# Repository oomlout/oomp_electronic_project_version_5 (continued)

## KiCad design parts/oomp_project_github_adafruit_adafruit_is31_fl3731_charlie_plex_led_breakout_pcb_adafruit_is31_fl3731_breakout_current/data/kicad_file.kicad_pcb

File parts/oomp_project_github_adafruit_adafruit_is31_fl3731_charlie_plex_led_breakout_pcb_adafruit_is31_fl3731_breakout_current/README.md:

# Project adafruit/Adafruit-IS31FL3731-CharliePlex-LED-Breakout-PCB Adafruit IS31 FL3731 Breakout current

[View the project on GitHub](https://github.com/adafruit/Adafruit-IS31FL3731-CharliePlex-LED-Breakout-PCB/blob/master/Adafruit%20IS31FL3731%20Breakout.brd)

[Open the interactive board explorer (GitHub Pages)](https://oomlout.github.io/oomp_electronic_project_version_5/parts/oomp_project_github_adafruit_adafruit_is31_fl3731_charlie_plex_led_breakout_pcb_adafruit_is31_fl3731_breakout_current/board_explorer.html)

[Browse this project category](../../navigation/oomp/project/github/adafruit/adafruit_is31_fl3731_charlie_plex_led_breakout_pcb/adafruit_is31_fl3731_breakout/README.md)

Project adafruit/Adafruit-IS31FL3731-CharliePlex-LED-Breakout-PCB Adafruit IS31 FL3731 Breakout current is a KiCad project containing 39 extracted component records. The catalogue matcher linked 18 physical placements to OOMP parts.

## Project snapshot

| Item | Count |
| --- | ---: |
| Components | 39 |
| PCB footprints | 26 |
| Mounting and locating holes | 4 |
| Matched OOMP mounting-hole items | 4 |
| Schematic symbols | 38 |
| Matched OOMP components | 18 |
| Unmatched physical components | 1 |
| Front-side placements | 15 |
| Back-side placements | 0 |
| Project version | `current` |
| Git ref | `master` |

## Board

[Original KiCad files](https://github.com/oomlout/oomp_electronic_project_version_5/tree/main/parts/oomp_project_github_adafruit_adafruit_is31_fl3731_charlie_plex_led_breakout_pcb_adafruit_is31_fl3731_breakout_current/data/original) · [OOMP KiCad design and local libraries](https://github.com/oomlout/oomp_electronic_project_version_5/tree/main/parts/oomp_project_github_adafruit_adafruit_is31_fl3731_charlie_plex_led_breakout_pcb_adafruit_is31_fl3731_breakout_current/data/oomp_design) · [Conversion / skipped-item report](https://github.com/oomlout/oomp_electronic_project_version_5/blob/main/parts/oomp_project_github_adafruit_adafruit_is31_fl3731_charlie_plex_led_breakout_pcb_adafruit_is31_fl3731_breakout_current/data/oomp_design/conversion_report.yaml)

The OOMP design is a separate copy. Only symbols and footprints verified against unchanged installed KiCad masters are replaced; custom and modified items are retained.

- Approximate size: **43.18 mm × 27.94 mm**
- Outline source: `KiCad Edge.Cuts`
- Placement drawing: [view `board.svg`](https://github.com/oomlout/oomp_electronic_project_version_5/blob/main/parts/oomp_project_github_adafruit_adafruit_is31_fl3731_charlie_plex_led_breakout_pcb_adafruit_is31_fl3731_breakout_current/data/generated_data/src/board.svg)
- PNG placement drawing: [view `board.png`](https://github.com/oomlout/oomp_electronic_project_version_5/blob/main/parts/oomp_project_github_adafruit_adafruit_is31_fl3731_charlie_plex_led_breakout_pcb_adafruit_is31_fl3731_breakout_current/data/generated_data/src/board.png)
- 300-pixel placement preview: [view `board_300.png`](https://github.com/oomlout/oomp_electronic_project_version_5/blob/main/parts/oomp_project_github_adafruit_adafruit_is31_fl3731_charlie_plex_led_breakout_pcb_adafruit_is31_fl3731_breakout_current/data/generated_data/src/board_300.png)
- Placement drawing with pin names: [view `board_pins.svg`](https://github.com/oomlout/oomp_electronic_project_version_5/blob/main/parts/oomp_project_github_adafruit_adafruit_is31_fl3731_charlie_plex_led_breakout_pcb_adafruit_is31_fl3731_breakout_current/data/generated_data/src/board_pins.svg)
- PNG drawing with pin names: [view `board_pins.png`](https://github.com/oomlout/oomp_electronic_project_version_5/blob/main/parts/oomp_project_github_adafruit_adafruit_is31_fl3731_charlie_plex_led_breakout_pcb_adafruit_is31_fl3731_breakout_current/data/generated_data/src/board_pins.png)
- 300-pixel pin preview: [view `board_pins_300.png`](https://github.com/oomlout/oomp_electronic_project_version_5/blob/main/parts/oomp_project_github_adafruit_adafruit_is31_fl3731_charlie_plex_led_breakout_pcb_adafruit_is31_fl3731_breakout_current/data/generated_data/src/board_pins_300.png)
- Bottom placement drawing: [view `board_bottom.svg`](https://github.com/oomlout/oomp_electronic_project_version_5/blob/main/parts/oomp_project_github_adafruit_adafruit_is31_fl3731_charlie_plex_led_breakout_pcb_adafruit_is31_fl3731_breakout_current/data/generated_data/src/board_bottom.svg)
- Bottom PNG placement drawing: [view `board_bottom.png`](https://github.com/oomlout/oomp_electronic_project_version_5/blob/main/parts/oomp_project_github_adafruit_adafruit_is31_fl3731_charlie_plex_led_breakout_pcb_adafruit_is31_fl3731_breakout_current/data/generated_data/src/board_bottom.png)
- 300-pixel bottom preview: [view `board_bottom_300.png`](https://github.com/oomlout/oomp_electronic_project_version_5/blob/main/parts/oomp_project_github_adafruit_adafruit_is31_fl3731_charlie_plex_led_breakout_pcb_adafruit_is31_fl3731_breakout_current/data/generated_data/src/board_bottom_300.png)
- Bottom placement drawing with pin names: [view `board_pins_bottom.svg`](https://github.com/oomlout/oomp_electronic_project_version_5/blob/main/parts/oomp_project_github_adafruit_adafruit_is31_fl3731_charlie_plex_led_breakout_pcb_adafruit_is31_fl3731_breakout_current/data/generated_data/src/board_pins_bottom.svg)
- Bottom PNG drawing with pin names: [view `board_pins_bottom.png`](https://github.com/oomlout/oomp_electronic_project_version_5/blob/main/parts/oomp_project_github_adafruit_adafruit_is31_fl3731_charlie_plex_led_breakout_pcb_adafruit_is31_fl3731_breakout_current/data/generated_data/src/board_pins_bottom.png)
- 300-pixel bottom pin preview: [view `board_pins_bottom_300.png`](https://github.com/oomlout/oomp_electronic_project_version_5/blob/main/parts/oomp_project_github_adafruit_adafruit_is31_fl3731_charlie_plex_led_breakout_pcb_adafruit_is31_fl3731_breakout_current/data/generated_data/src/board_pins_bottom_300.png)
- Mechanical drawing: [view `board_mechanical.svg`](https://github.com/oomlout/oomp_electronic_project_version_5/blob/main/parts/oomp_project_github_adafruit_adafruit_is31_fl3731_charlie_plex_led_breakout_pcb_adafruit_is31_fl3731_breakout_current/data/generated_data/src/board_mechanical.svg)
- Mechanical PNG: [view `board_mechanical.png`](https://github.com/oomlout/oomp_electronic_project_version_5/blob/main/parts/oomp_project_github_adafruit_adafruit_is31_fl3731_charlie_plex_led_breakout_pcb_adafruit_is31_fl3731_breakout_current/data/generated_data/src/board_mechanical.png)
- 300-pixel mechanical preview: [view `board_mechanical_300.png`](https://github.com/oomlout/oomp_electronic_project_version_5/blob/main/parts/oomp_project_github_adafruit_adafruit_is31_fl3731_charlie_plex_led_breakout_pcb_adafruit_is31_fl3731_breakout_current/data/generated_data/src/board_mechanical_300.png)
- Open the board explorer on GitHub Pages: [explore this board](https://oomlout.github.io/oomp_electronic_project_version_5/parts/oomp_project_github_adafruit_adafruit_is31_fl3731_charlie_plex_led_breakout_pcb_adafruit_is31_fl3731_breakout_current/board_explorer.html)
- InteractiveHtmlBom generation is configured; install KiCad or set `KICAD_PYTHON` to its bundled Python to build `data/interactivehtmlbom/ibom.html`.

## Board with pins

## Bottom board with pins

The bottom view is mirrored horizontally so it is shown as viewed from beneath the assembled board.

## Mechanical layer

The table uses a board-relative origin at the minimum X/Y point of `Edge.Cuts`. This point is shown as **0,0** in the mechanical drawing; X increases right and Y increases down. Original KiCad coordinates are retained alongside it.

### Diameter 2.5 mm holes

| OOMP reference | Source | Name | Classification | Role | Board X (mm) | Board Y (mm) | OOMP part |
| --- | --- | --- | --- | --- | ---: | ---: | --- |
| `MH1` | `U$3` | Mounting Hole 2.5 mm Round Plated | `mechanical / mounting_hole / 2_5_mm / round / plated` | mounting | 2.540 | 25.400 | [`mechanical_mounting_hole_2_5_mm_round_plated`](https://github.com/oomlout/oomp_electronic_version_5/tree/main/parts/mechanical_mounting_hole_2_5_mm_round_plated) |
| `MH2` | `U$4` | Mounting Hole 2.5 mm Round Plated | `mechanical / mounting_hole / 2_5_mm / round / plated` | mounting | 40.640 | 25.400 | [`mechanical_mounting_hole_2_5_mm_round_plated`](https://github.com/oomlout/oomp_electronic_version_5/tree/main/parts/mechanical_mounting_hole_2_5_mm_round_plated) |
| `MH3` | `U$5` | Mounting Hole 2.5 mm Round Plated | `mechanical / mounting_hole / 2_5_mm / round / plated` | mounting | 2.540 | 2.540 | [`mechanical_mounting_hole_2_5_mm_round_plated`](https://github.com/oomlout/oomp_electronic_version_5/tree/main/parts/mechanical_mounting_hole_2_5_mm_round_plated) |
| `MH4` | `U$6` | Mounting Hole 2.5 mm Round Plated | `mechanical / mounting_hole / 2_5_mm / round / plated` | mounting | 40.640 | 2.540 | [`mechanical_mounting_hole_2_5_mm_round_plated`](https://github.com/oomlout/oomp_electronic_version_5/tree/main/parts/mechanical_mounting_hole_2_5_mm_round_plated) |

## Bill of materials

| References | Quantity | Description | Value | Footprint | OOMP part |
| --- | ---: | --- | --- | --- | --- |
| C1, C4 | 2 | Capacitor 10 uF 0805 | 10uF | `Adafruit IS31FL3731 Breakout-import-fps:0805-NO` | [`electronic_capacitor_0805_10_micro_farad`](https://github.com/oomlout/oomp_electronic_version_5/tree/main/parts/electronic_capacitor_0805_10_micro_farad) |
| C2, C5 | 2 | Capacitor 100 nF 0805 | 0.1uF | `Adafruit IS31FL3731 Breakout-import-fps:0805-NO` | [`electronic_capacitor_0805_100_nano_farad`](https://github.com/oomlout/oomp_electronic_version_5/tree/main/parts/electronic_capacitor_0805_100_nano_farad) |
| C3 | 1 | Capacitor 220 nF 0805 | 0.22uF | `Adafruit IS31FL3731 Breakout-import-fps:0805-NO` | [`electronic_capacitor_0805_220_nano_farad`](https://github.com/oomlout/oomp_electronic_version_5/tree/main/parts/electronic_capacitor_0805_220_nano_farad) |
| JP2, JP4 | 2 | Connector Header PZ254-1-13-Z-8.5 |  | `Adafruit IS31FL3731 Breakout-import-fps:1X13_ROUND_70` | [`electronic_connector_header_2_54_mm_pitch_through_hole_13_pin`](https://github.com/oomlout/oomp_electronic_version_5/tree/main/parts/electronic_connector_header_2_54_mm_pitch_through_hole_13_pin) |
| JP5 | 1 | Connector Header PH2.54-01-07PZD |  | `Adafruit IS31FL3731 Breakout-import-fps:1X07_ROUND_76` | [`electronic_connector_header_2_54_mm_pitch_through_hole_7_pin`](https://github.com/oomlout/oomp_electronic_version_5/tree/main/parts/electronic_connector_header_2_54_mm_pitch_through_hole_7_pin) |
| R1 | 1 | Resistor 20000 Ohm 0805 | 20K | `Adafruit IS31FL3731 Breakout-import-fps:0805-THM` | [`electronic_resistor_0805_20000_ohm`](https://github.com/oomlout/oomp_electronic_version_5/tree/main/parts/electronic_resistor_0805_20000_ohm) |
| R2, R3, R4, R5, R6 | 5 | Resistor 20000 Ohm 0805 | 20K | `Adafruit IS31FL3731 Breakout-import-fps:0805-NO` | [`electronic_resistor_0805_20000_ohm`](https://github.com/oomlout/oomp_electronic_version_5/tree/main/parts/electronic_resistor_0805_20000_ohm) |
| U1 | 1 | IS31FL3731-SALS2 | IS31FL3731-SALS2 | `Adafruit IS31FL3731 Breakout-import-fps:QFN28_4MM_0.4MM` | unmatched |

## Main nets

| Net | Pads | Components |
| --- | ---: | --- |
| `VCC` | 11 | C1, C4, C5, JP2, JP5, R2, R3, R4, R5, SJ1, U1 |
| `GND` | 10 | C1, C2, C4, C5, JP2, JP5, R1, R6, U1 |
| `ADDR` | 6 | JP4, R6, SJ1, SJ2, SJ3, U1 |
| `SCL` | 5 | JP2, JP5, R4, SJ2, U1 |
| `SDA` | 5 | JP2, JP5, R3, SJ3, U1 |
| `INTB` | 4 | JP4, JP5, R5, U1 |
| `SHUTDOWN` | 4 | JP4, JP5, R2, U1 |
| `AUDIOIN` | 3 | C3, JP4, JP5 |
| `CA1` | 2 | JP4, U1 |
| `CA2` | 2 | JP4, U1 |
| `CA3` | 2 | JP4, U1 |
| `CA4` | 2 | JP4, U1 |
| `CA5` | 2 | JP4, U1 |
| `CA6` | 2 | JP4, U1 |
| `CA7` | 2 | JP4, U1 |
| `CA8` | 2 | JP4, U1 |
| `CA9` | 2 | JP4, U1 |
| `CB1` | 2 | JP2, U1 |
| `CB2` | 2 | JP2, U1 |
| `CB3` | 2 | JP2, U1 |

## Design notes

- The extracted board outline is approximately 43.18 mm by 27.94 mm.
- Placement data contains 15 front-side and 0 back-side components.

## Review notes

- 1 physical component records are not yet matched to an OOMP part.

- Part identities needing a manufacturer/LCSC decision: [`lcsc_review.yaml`](https://github.com/oomlout/oomp_electronic_project_version_5/blob/main/parts/oomp_project_github_adafruit_adafruit_is31_fl3731_charlie_plex_led_breakout_pcb_adafruit_is31_fl3731_breakout_current/data/generated_data/lcsc_review.yaml)
- Browser-only research and datasheet queue: [`browser_research_queue.md`](https://github.com/oomlout/oomp_electronic_project_version_5/blob/main/parts/oomp_project_github_adafruit_adafruit_is31_fl3731_charlie_plex_led_breakout_pcb_adafruit_is31_fl3731_breakout_current/data/generated_data/browser_research_queue.md)

## Generated source bundle

- Project image assets: [`data/generated_data/src`](https://github.com/oomlout/oomp_electronic_project_version_5/tree/main/parts/oomp_project_github_adafruit_adafruit_is31_fl3731_charlie_plex_led_breakout_pcb_adafruit_is31_fl3731_breakout_current/data/generated_data/src)
- Copied component source manifest: `data/project_source/manifest.yaml` (generated locally and ignored by Git)
- Matched OOMP source parts copied: 7

## Source files

- Schematic: `data/kicad_file.kicad_sch`
- PCB: `data/kicad_file.kicad_pcb`

---

Generated deterministically by `kicad_agents.project_summary_agent`; no LLM-authored content is used.

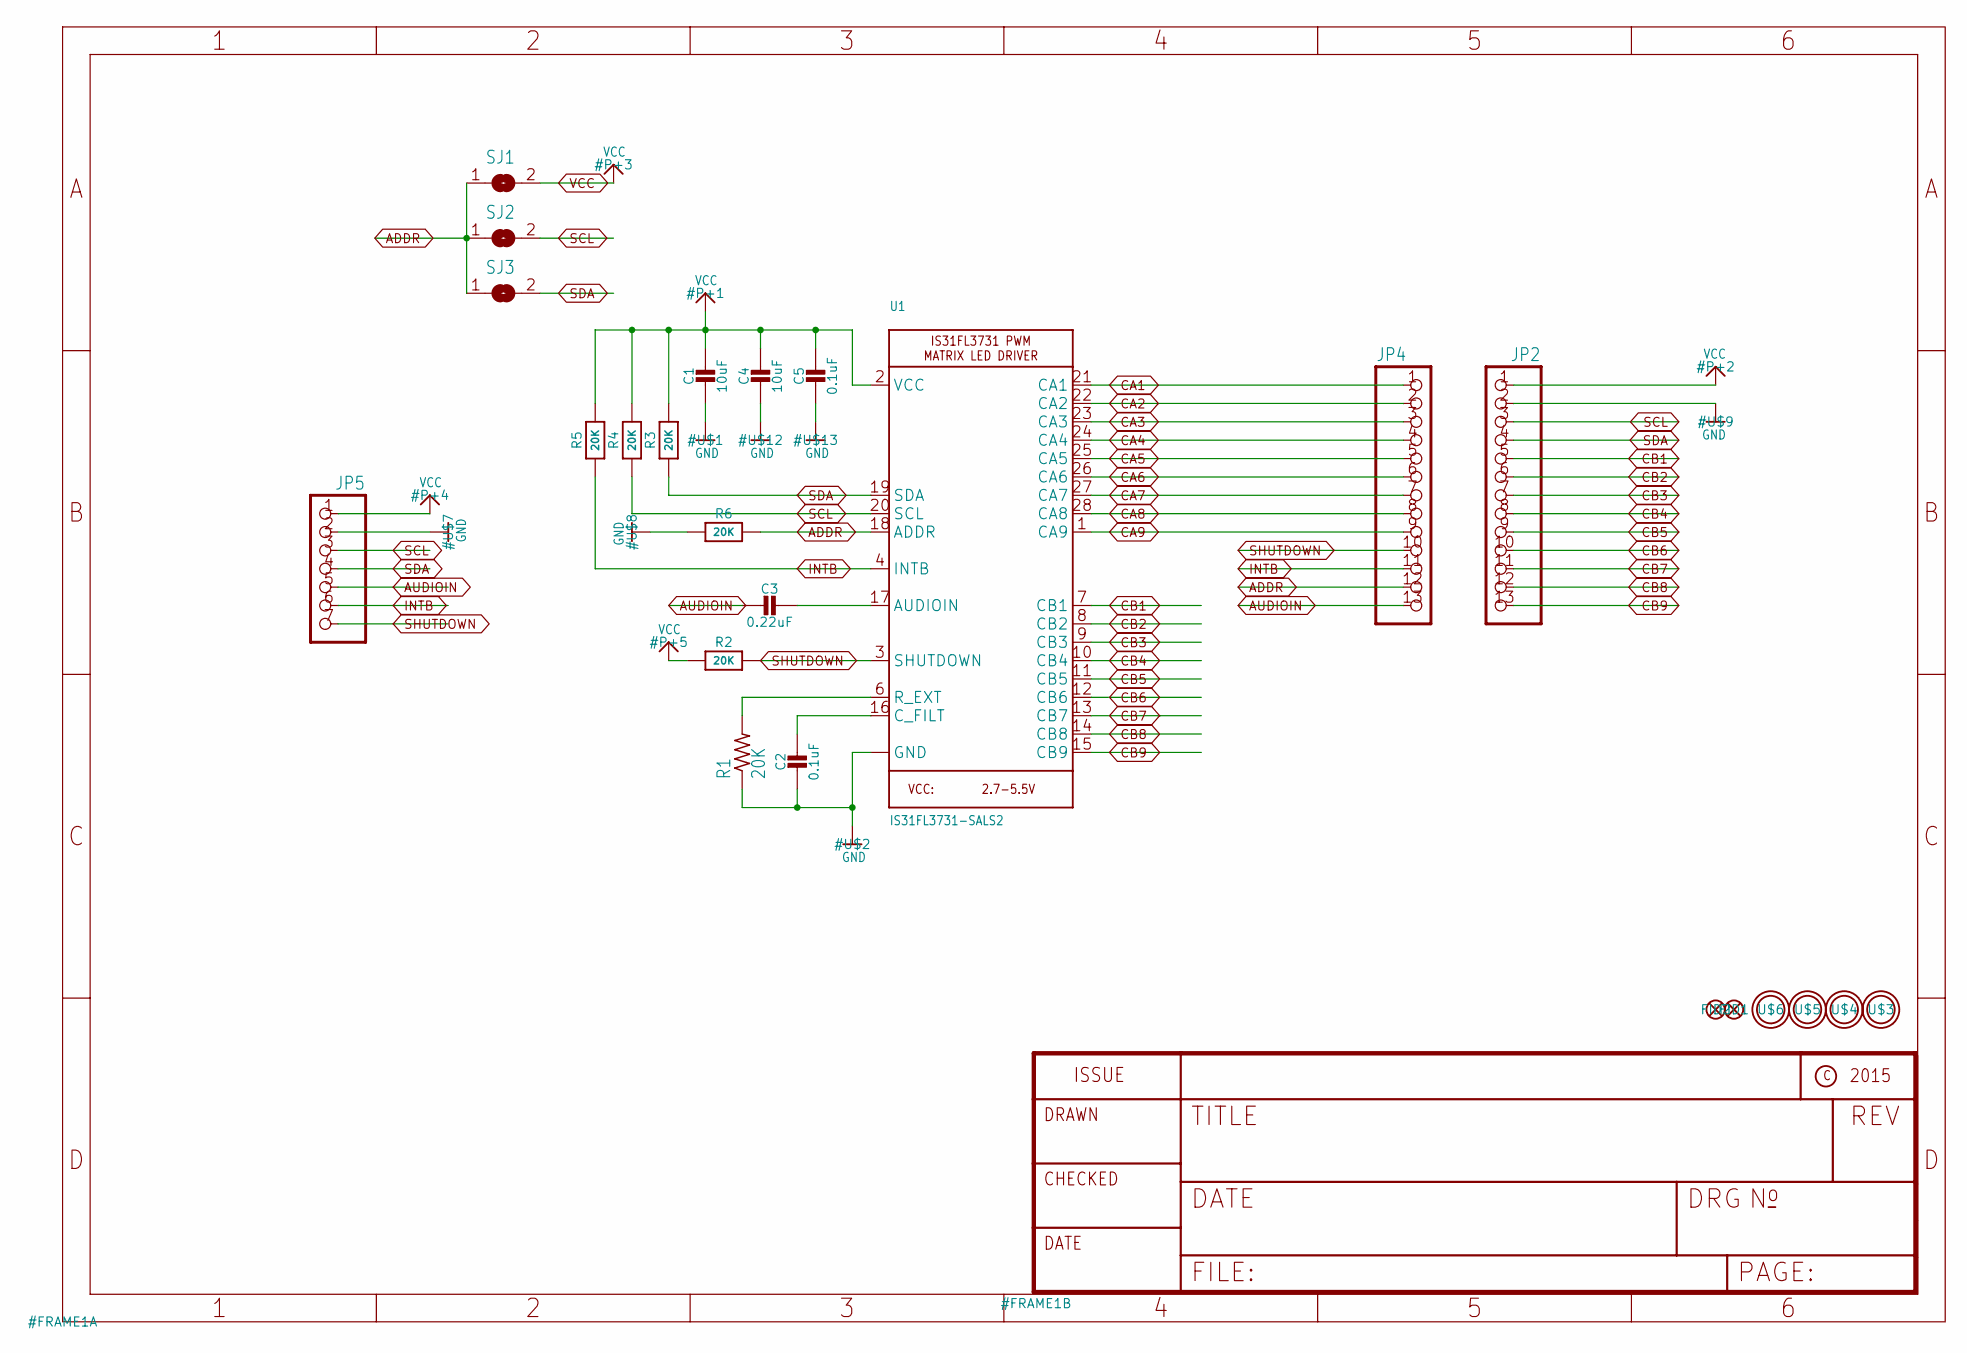
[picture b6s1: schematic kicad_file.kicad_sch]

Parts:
C1, C4: 10uF; 0805-NO
C2, C5: 0.1uF; 0805-NO
C3: 0.22uF; 0805-NO
FID1, FID2: FIDUCIAL""; FIDUCIAL_1MM
JP2, JP4: HEADER-1X13; 1X13_ROUND_70
JP5: HEADER-1X7THICKER; 1X07_ROUND_76
R1: 20K; 0805-THM
R2, R3, R4, R5, R6: 20K; 0805-NO
SJ1, SJ2, SJ3: SOLDERJUMPER; SOLDERJUMPER_ARROW_NOPASTE
U1: IS31FL3731-SALS2; QFN28_4MM_0.4MM
U$3, U$4, U$5, U$6: MOUNTINGHOLE2.5; MOUNTINGHOLE_2.5_PLATED

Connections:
ADDR: JP4.12, R6.2, SJ1.1, SJ2.1, SJ3.1, U1.18 (ADDR)
AUDIOIN: C3.2, JP4.13, JP5.5
CA1: JP4.1, U1.21 (CA1)
CA2: JP4.2, U1.22 (CA2)
CA3: JP4.3, U1.23 (CA3)
CA4: JP4.4, U1.24 (CA4)
CA5: JP4.5, U1.25 (CA5)
CA6: JP4.6, U1.26 (CA6)
CA7: JP4.7, U1.27 (CA7)
CA8: JP4.8, U1.28 (CA8)
CA9: JP4.9, U1.1 (CA9)
CB1: JP2.5, U1.7 (CB1)
CB2: JP2.6, U1.8 (CB2)
CB3: JP2.7, U1.9 (CB3)
CB4: JP2.8, U1.10 (CB4)
CB5: JP2.9, U1.11 (CB5)
CB6: JP2.10, U1.12 (CB6)
CB7: JP2.11, U1.13 (CB7)
CB8: JP2.12, U1.14 (CB8)
CB9: JP2.13, U1.15 (CB9)
GND: C1.2, C2.2, C4.2, C5.2, JP2.2, JP5.2, R1.1, R6.1, U1.5 (GND), U1.THERMAL (GND)
INTB: JP4.11, JP5.6, R5.1, U1.4 (INTB)
unnamed: C2.1, U1.16 (C_FILT)
unnamed: R1.2, U1.6 (R_EXT)
unnamed: C3.1, U1.17 (AUDIOIN)
SCL: JP2.3, JP5.3, R4.1, SJ2.2, U1.20 (SCL)
SDA: JP2.4, JP5.4, R3.1, SJ3.2, U1.19 (SDA)
SHUTDOWN: JP4.10, JP5.7, R2.2, U1.3 (SHUTDOWN)
VCC: C1.1, C4.1, C5.1, JP2.1, JP5.1, R2.1, R3.2, R4.2, R5.2, SJ1.2, U1.2 (VCC)

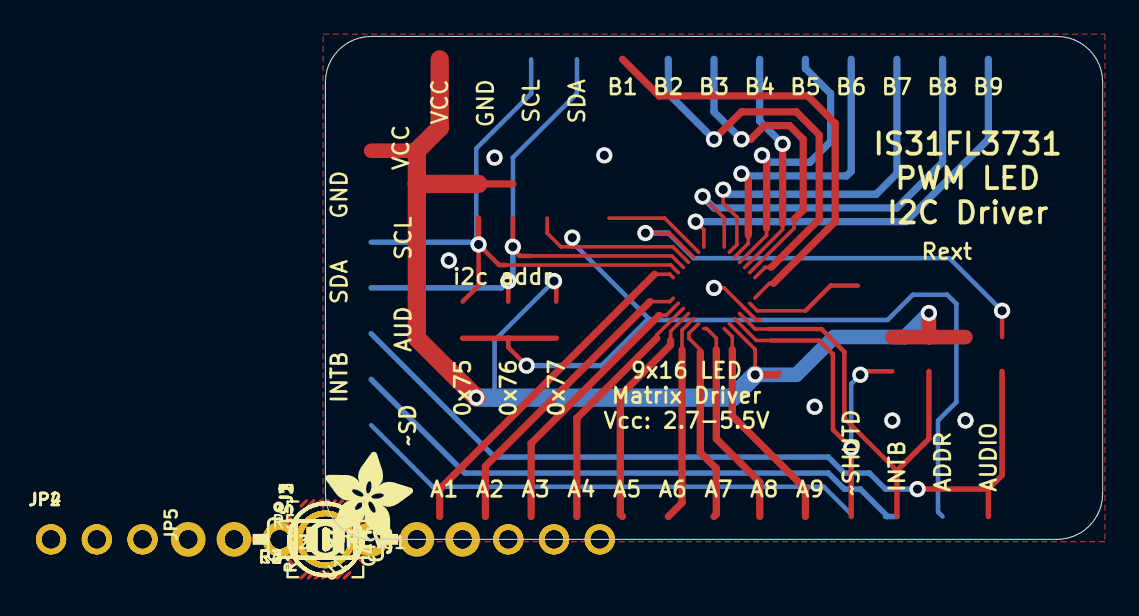
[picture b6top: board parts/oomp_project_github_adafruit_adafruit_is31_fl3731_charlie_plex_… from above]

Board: 2 copper layers, 43.2 x 27.9 mm, 26 parts (0 on the bottom side), 29 nets.

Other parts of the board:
U$10: ADAFRUIT_5MM
U$11: PCBFEAT-REV-040

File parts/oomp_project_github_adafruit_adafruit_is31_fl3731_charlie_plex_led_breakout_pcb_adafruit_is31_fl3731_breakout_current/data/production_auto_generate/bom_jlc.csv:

Comment,Designator,Footprint,LCSC Part #
,JP5,Adafruit IS31FL3731 Breakout-import-fps:1X07_ROUND_76,C7501585
,"JP2,JP4",Adafruit IS31FL3731 Breakout-import-fps:1X13_ROUND_70,C2894936
,U$10,Adafruit IS31FL3731 Breakout-import-fps:ADAFRUIT_5MM,
,U$11,Adafruit IS31FL3731 Breakout-import-fps:PCBFEAT-REV-040,
0.1uF,"C2,C5",Adafruit IS31FL3731 Breakout-import-fps:0805-NO,
0.22uF,C3,Adafruit IS31FL3731 Breakout-import-fps:0805-NO,
10uF,"C1,C4",Adafruit IS31FL3731 Breakout-import-fps:0805-NO,
20K,"R2,R3,R4,R5,R6",Adafruit IS31FL3731 Breakout-import-fps:0805-NO,
20K,R1,Adafruit IS31FL3731 Breakout-import-fps:0805-THM,
IS31FL3731-SALS2,U1,Adafruit IS31FL3731 Breakout-import-fps:QFN28_4MM_0.4MM,

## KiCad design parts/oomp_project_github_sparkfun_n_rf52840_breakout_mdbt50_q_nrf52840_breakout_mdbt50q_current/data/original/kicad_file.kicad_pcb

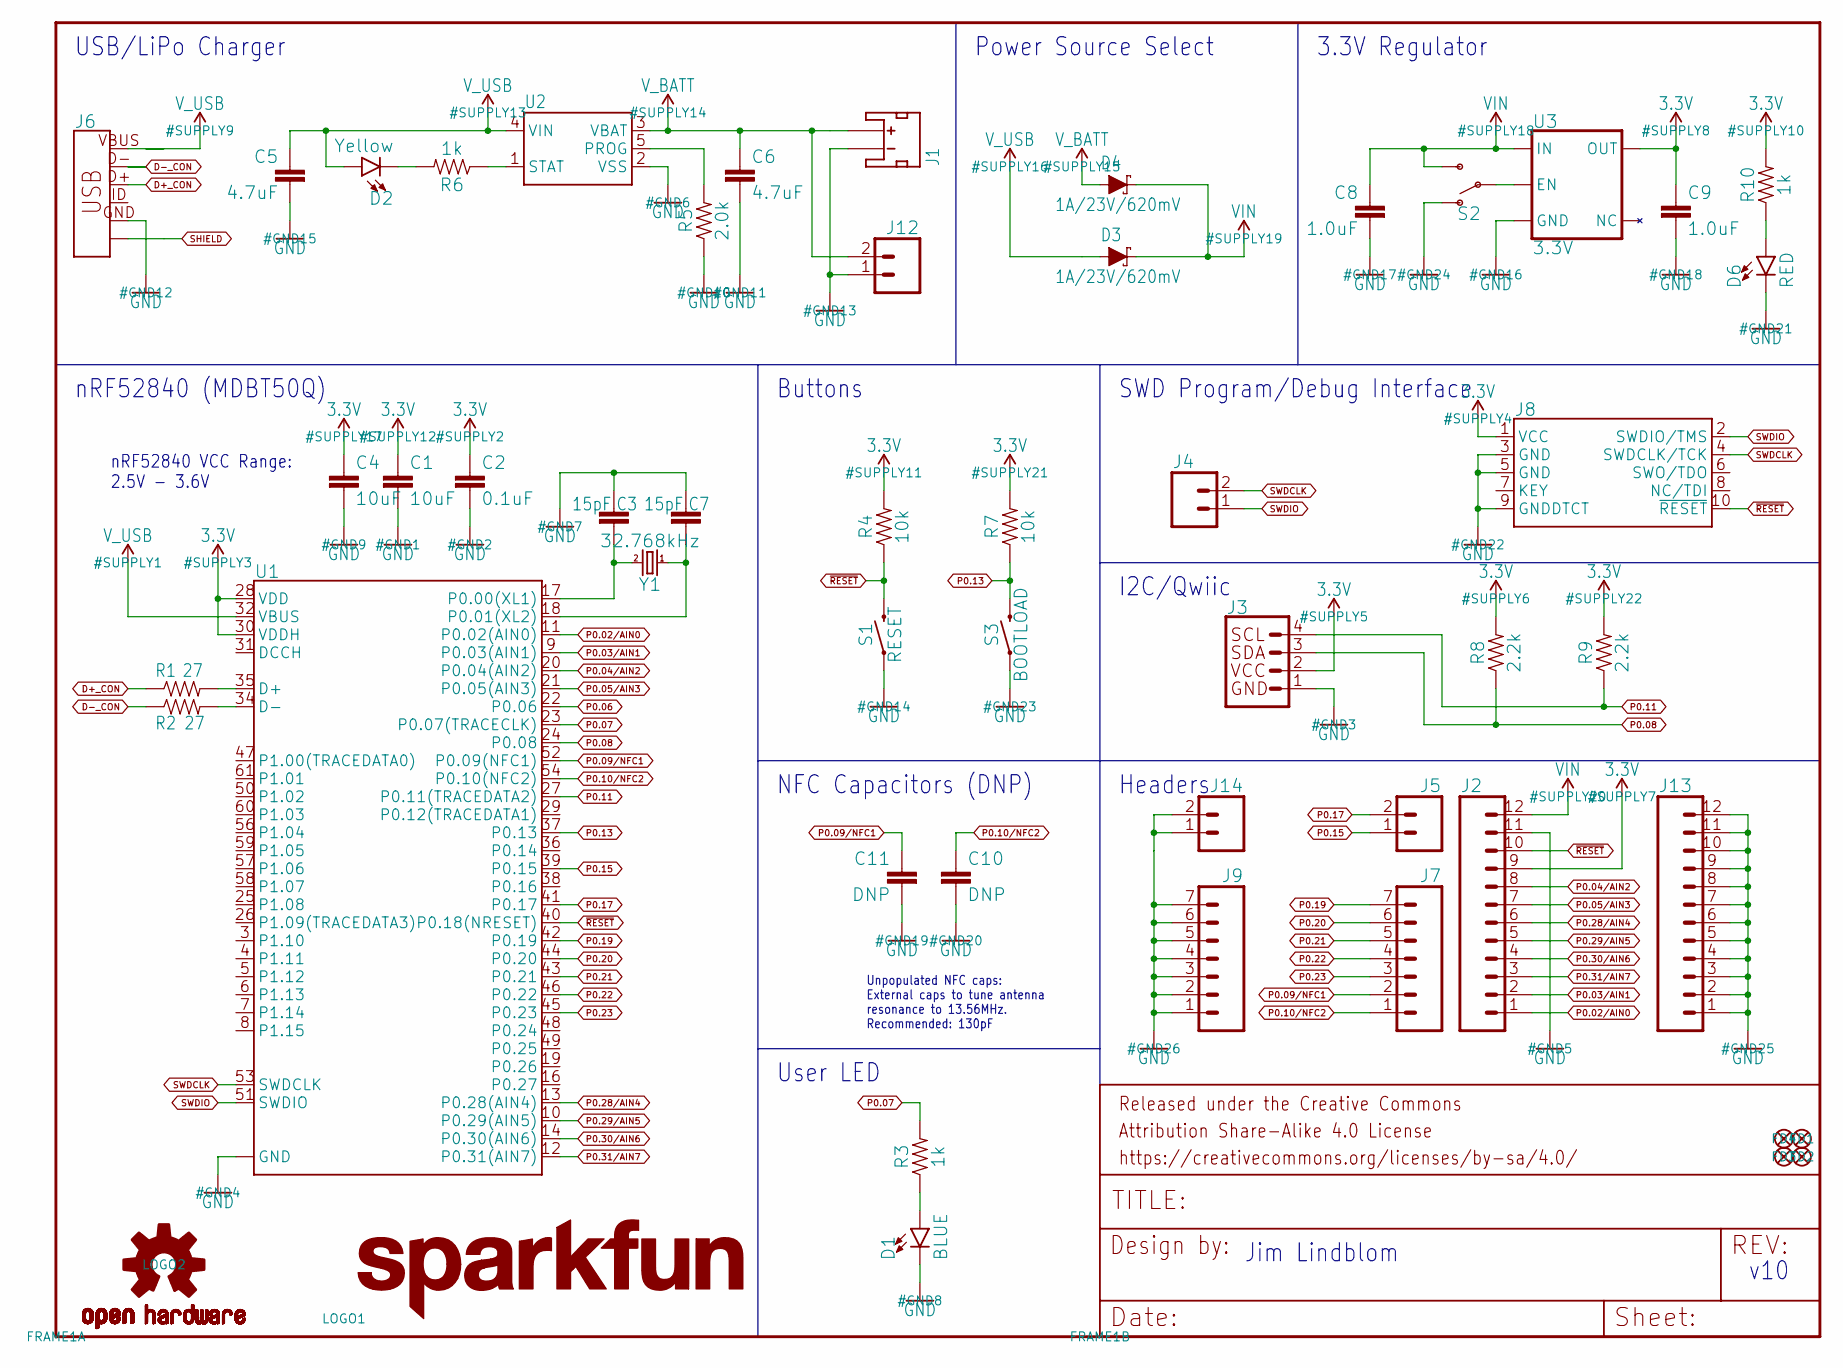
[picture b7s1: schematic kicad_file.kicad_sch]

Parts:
C1, C4: 10uF; 0603
C2: 0.1uF; 0603
C3, C7: 15pF; 0603
C5, C6: 4.7uF; 0603
C8, C9: 1.0uF; 0603
C10, C11: DNP; 0603
D1: BLUE; LED-0603
D2: Yellow; LED-0603
D3, D4: 1A/23V/620mV; SOD-323
D6: RED; LED-0603
FD1, FD2, FD3, FD4: FIDUCIALUFIDUCIAL; FIDUCIAL-MICRO
FRAME1: FRAME-LETTER; CREATIVE_COMMONS
J1: JST_2MM_MALESMD; JST-2-SMD
J2, J13: CONN_12NO_SILK; 1X12_NO_SILK
J3: QWIIC_CONNECTORJS-1MM; 1X04_1MM_RA
J4, J5, J12, J14: CONN_021X02_NO_SILK; 1X02_NO_SILK
J6: USB_MICRO-B_HALF_PTH_MILL; USB-MICROB-PTH-MILL
J7, J9: CONN_07NO_SILK; 1X07_NO_SILK
J8: CORTEX_DEBUG_PTH; 2X5-PTH-1.27MM
LOGO1: SFE_LOGO_NAME.2_INCH; SFE_LOGO_NAME_.2
LOGO2: OSHW-LOGOS; OSHW-LOGO-S
R1, R2: 27; 0603
R3, R6, R10: 1k; 0603
R4, R7: 10k; 0603
R5: 2.0k; 0603
R8, R9: 2.2k; 0603
S1: RESET; TACTILE_SWITCH_SMD_RIGHT_ANGLE
S2: SWITCH-SPDT-SMD-RIGHT-ANGLE; SWITCH_SPST_SMD_A
S3: BOOTLOAD; TACTILE_SWITCH_SMD_RIGHT_ANGLE
U1: MDBT50Q
U2: MCP73831; SOT23-5
U3: 3.3V; SOT23-5
Y1: 32.768kHz; CRYSTAL-SMD-3.2X1.5MM

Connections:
3.3V: C1.1, C2.1, C4.1, C9.1, J2.9, J3.2, J8.1 (VCC), R4.2, R7.2, R8.2, R9.2, R10.2, U1.28 (VDD), U1.30 (VDDH), U3.5 (OUT)
D+: R1.2, U1.35 (D+)
D+_CON: J6.D+, R1.1
D-: R2.2, U1.34 (D-)
D-_CON: J6.D-, R2.1
GND: C1.2, C2.2, C3.1, C4.2, C5.2, C6.2, C7.1, C8.2, C9.2, C10.2, C11.2, D1.C, D6.C, J1.1 (-), J2.11, J3.1, J6.GND, J8.3 (GND), J8.5 (GND), J8.9 (GNDDTCT), J9.1, J9.2, J9.3, J9.4, J9.5, J9.6, J9.7, J12.1, J13.1, J13.2, J13.3, J13.4, J13.5, J13.6, J13.7, J13.8, J13.9, J13.10, J13.11, J13.12, J14.1, J14.2, R5.1, S1.1, S2.1 (O), S3.1, U1.1 (GND), U1.2 (GND), U1.15 (GND), U1.33 (GND), U1.55 (GND), U2.2 (VSS), U3.2 (GND)
unnamed: R5.2, U2.5 (PROG)
unnamed: D2.C, R6.2
unnamed: R6.1, U2.1 (STAT)
unnamed: D1.A, R3.1
unnamed: D6.A, R10.1
P0.02/AIN0: J2.1, U1.11 (P0.02(AIN0))
P0.03/AIN1: J2.2, U1.9 (P0.03(AIN1))
P0.04/AIN2: J2.8, U1.20 (P0.04(AIN2))
P0.05/AIN3: J2.7, U1.21 (P0.05(AIN3))
P0.06: U1.22 (P0.06)
P0.07: R3.2, U1.23 (P0.07(TRACECLK))
P0.08: J3.3, R8.1, U1.24 (P0.08)
P0.09/NFC1: C11.1, J7.2, U1.52 (P0.09(NFC1))
P0.10/NFC2: C10.1, J7.1, U1.54 (P0.10(NFC2))
P0.11: J3.4, R9.1, U1.27 (P0.11(TRACEDATA2))
P0.13: R7.1, S3.2, U1.37 (P0.13)
P0.15: J5.1, U1.39 (P0.15)
P0.17: J5.2, U1.41 (P0.17)
P0.19: J7.7, U1.42 (P0.19)
P0.20: J7.6, U1.44 (P0.20)
P0.21: J7.5, U1.43 (P0.21)
P0.22: J7.4, U1.46 (P0.22)
P0.23: J7.3, U1.45 (P0.23)
P0.28/AIN4: J2.6, U1.13 (P0.28(AIN4))
P0.29/AIN5: J2.5, U1.10 (P0.29(AIN5))
P0.30/AIN6: J2.4, U1.14 (P0.30(AIN6))
P0.31/AIN7: J2.3, U1.12 (P0.31(AIN7))
SHIELD: J6.SHIELD, J6.SHIELD2 (SHIELD), J6.SHIELD3 (SHIELD), J6.SHIELD4 (SHIELD), J6.SHIELD5 (SHIELD), J6.SHIELD6 (SHIELD), J6.SHIELD7 (SHIELD), J6.SHIELD8 (SHIELD), J6.SHIELD9 (SHIELD), J6.SHIELD10 (SHIELD)
SWDCLK: J4.2, J8.4 (SWDCLK/TCK), U1.53 (SWDCLK)
SWDIO: J4.1, J8.2 (SWDIO/TMS), U1.51 (SWDIO)
VIN: C8.1, D3.C, D4.C, J2.12, S2.3 (S), U3.1 (IN)
VREG_EN: S2.2, U3.3 (EN)
V_BATT: C6.1, D4.A, J1.2 (+), J12.2, U2.3 (VBAT)
V_USB: C5.1, D2.A, D3.A, J6.VBUS, U1.32 (VBUS), U2.4 (VIN)
XL1: C3.2, U1.17 (P0.00(XL1)), Y1.P$2 (2)
XL2: C7.2, U1.18 (P0.01(XL2)), Y1.P$1 (1)
~RESET: J2.10, J8.10 (~RESET), R4.1, S1.2, U1.40 (P0.18(NRESET))

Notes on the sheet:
User LED
Buttons
Headers
3.3V Regulator
Jim Lindblom
nRF52840 (MDBT50Q)
NFC Capacitors (DNP)
SWD Program/Debug Interface
nRF52840 VCC Range: 2.5V - 3.6V
v10
I2C/Qwiic
USB/LiPo Charger
Power Source Select
Unpopulated NFC caps: External caps to tune antenna resonance to 13.56MHz. Recommended: 130pF

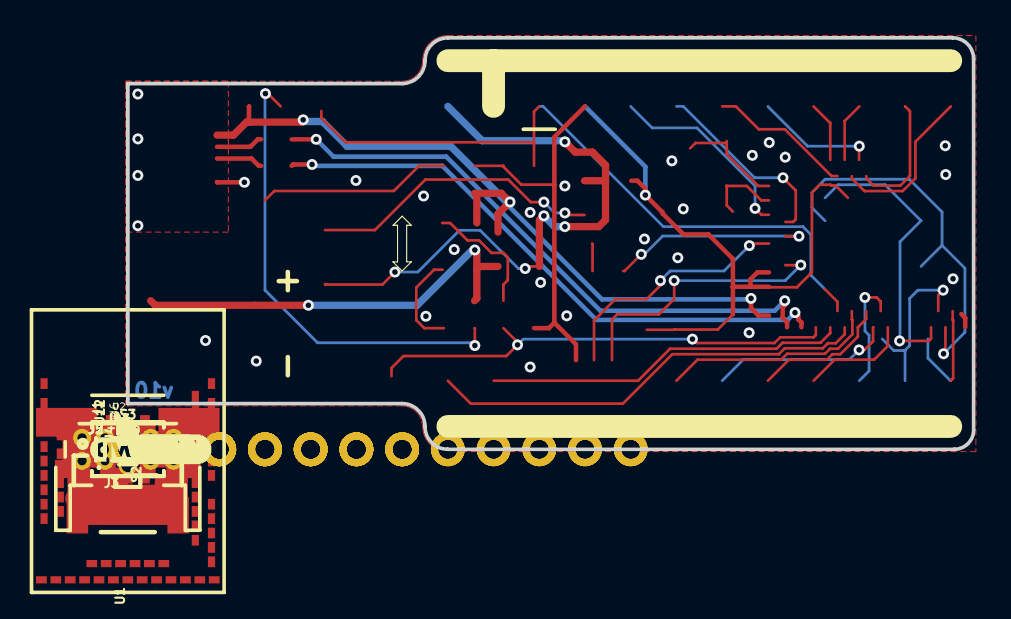
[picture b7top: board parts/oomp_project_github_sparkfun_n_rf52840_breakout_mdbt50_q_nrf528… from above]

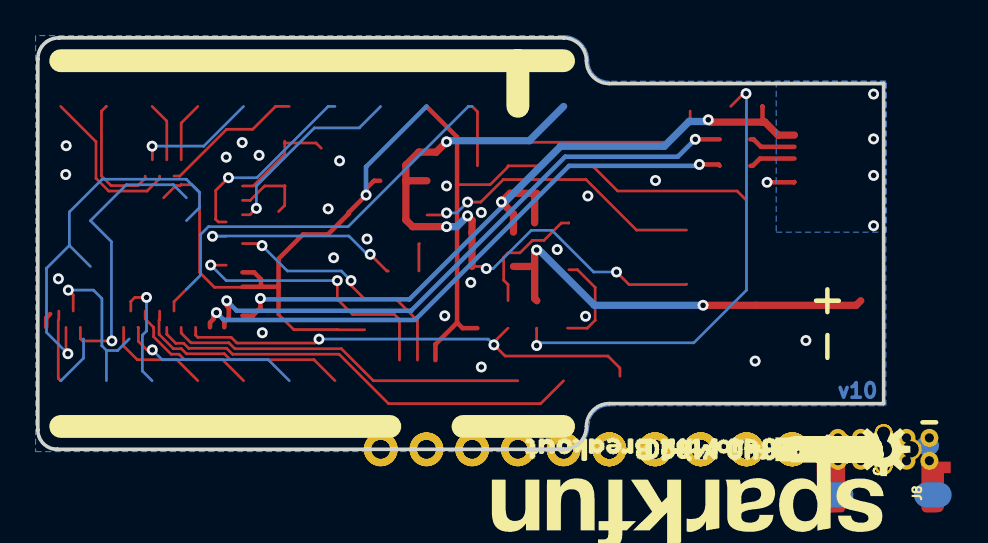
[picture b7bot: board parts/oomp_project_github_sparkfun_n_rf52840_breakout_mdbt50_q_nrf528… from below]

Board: 2 copper layers, 47.0 x 22.9 mm, 110 parts (37 on the bottom side), 42 nets.

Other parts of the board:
U$1: 3V316
U$2: 130
U$3: RST19
U$4: ON1
U$5: CHG26
U$6: PWR27
U$7: GND17
U$8: QWIIC#LOGO#JPG
U$9: 20
U$10: 31
U$11: 292
U$12: 313
U$13: 3V30
U$14: 285
U$15: 521
U$16: 421
U$17: HTTP###SFE#IO#T8200
U$18: #RST6
U$19: GND7
U$20: VIN8
U$21: 1022
U$22: 916
U$23: 2111
U$24: 1912
U$25: 1713
U$26: 1522
U$27: VIN19
U$28: 70
U$29: NRF52840_MINI_BREAKOUT0
U$30: GND6
U$31: 27
U$32: 36
U$33: SWD0
U$34: 315
U$35: 300
U$36: 301
U$37: 293
U$38: 108
U$39: 51
U$40: 40
U$41: 97
U$42: 236
U$43: 200
U$44: 225
U$45: 221
U$46: 214
U$47: 203
U$48: 192
U$49: 151
U$50: 170
U$51: RST1
U$52: ANALOG2
U$53: 232
U$54: SCL#114
U$55: SDA#83
U$56: IO2
U$57: CLK1
U$58: OFF2

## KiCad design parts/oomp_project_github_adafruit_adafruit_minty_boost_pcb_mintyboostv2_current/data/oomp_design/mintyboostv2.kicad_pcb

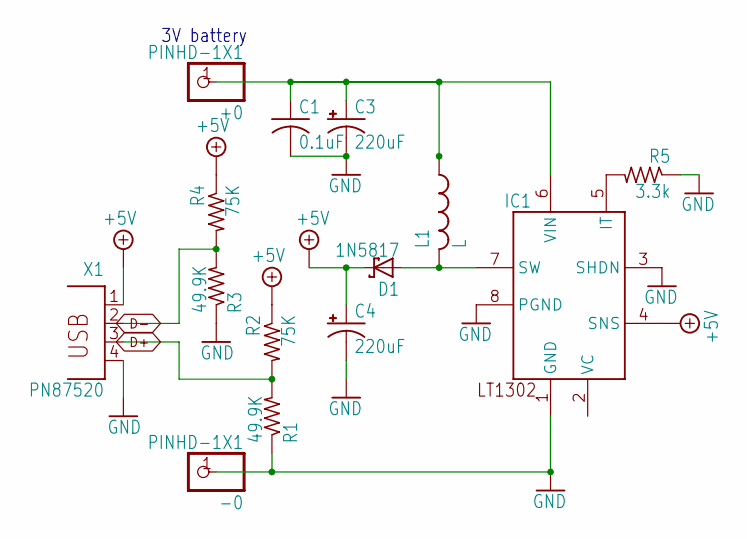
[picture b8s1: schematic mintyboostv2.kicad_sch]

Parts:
+0: PINHD-1X1; 1X01
-0: PINHD-1X1; 1X01
C1: 0.1uF; C025-025X050
C3, C4: 220uF; E2,5-5
D1: 1N5817; DO41-7
IC1: LT1302; DIL08
L1: L; 6000
R1, R3: 49.9K; 0204_5
R2, R4: 75K; 0204_5
R5: 3.3k; 0204_5
X1: PN87520

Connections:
+5V: C4.+, D1.C, IC1.4 (SNS), R2.1, R4.1, X1.1
BATT+: +0.1, C1.1, C3.+, IC1.6 (VIN), L1.1
D+: R1.2, R2.2, X1.3
D-: R3.2, R4.2, X1.2
GND: -0.1, C1.2, C3.-, C4.-, IC1.1 (GND), IC1.3 (SHDN), IC1.8 (PGND), R1.1, R3.1, R5.1, X1.4
unnamed: IC1.5 (IT), R5.2
unnamed: D1.A, IC1.7 (SW), L1.2

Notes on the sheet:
3V battery

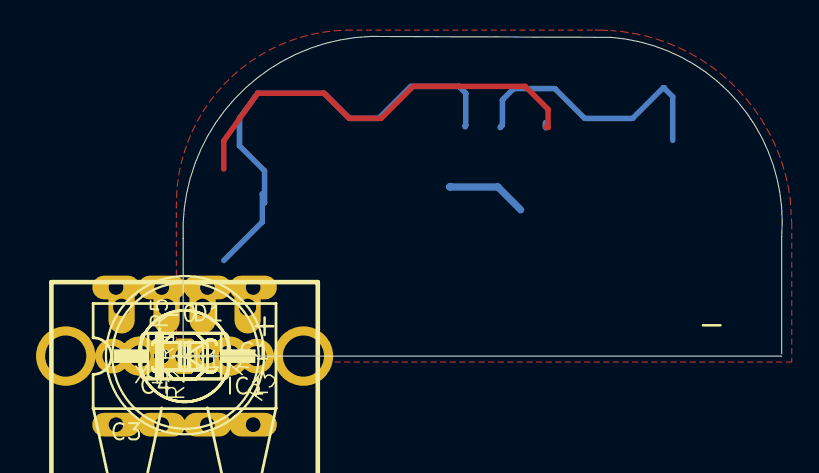
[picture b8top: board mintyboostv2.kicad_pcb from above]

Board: 16 copper layers, 33.3 x 17.8 mm, 14 parts (0 on the bottom side), 7 nets.
